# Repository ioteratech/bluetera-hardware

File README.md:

# Bluetera Hardware

This repository contains the KiCad project for the Bluetera II and it's breakout adapter.

Bluetera is an open source IoT platform for the development of smart and connected products. The platform includes:
* Bluetera Hardware module (this repository)
* Bluetera Firmware - repository [here](https://github.com/ioteratech/bluetera-firmware)
* Blutera SDK(s) - repositories [here](https://github.com/ioteratech/)

More info available at our website: https://ioteratech.com

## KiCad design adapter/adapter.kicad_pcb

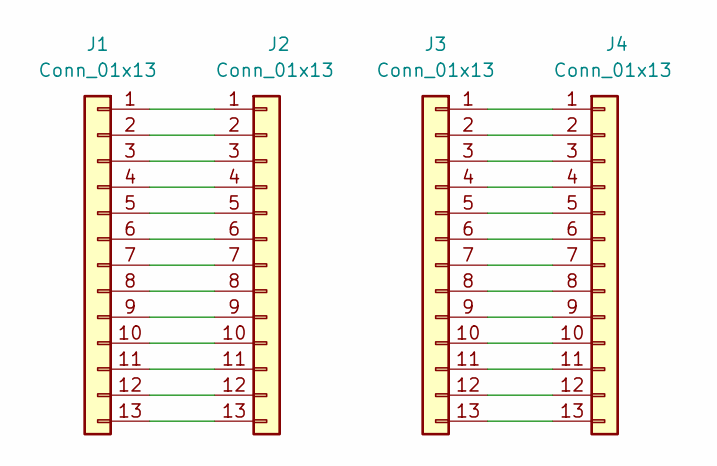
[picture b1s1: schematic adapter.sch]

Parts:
J1, J4: Conn_01x13; PinHeader_1x13_P2.54mm_Vertical
J2, J3: Conn_01x13; PinHeader_1x13_P1.27mm_Vertical

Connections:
unnamed: J1.1, J2.1
unnamed: J1.2, J2.2
unnamed: J1.3, J2.3
unnamed: J1.4, J2.4
unnamed: J1.5, J2.5
unnamed: J1.6, J2.6
unnamed: J1.7, J2.7
unnamed: J1.8, J2.8
unnamed: J1.9, J2.9
unnamed: J1.10, J2.10
unnamed: J1.11, J2.11
unnamed: J1.12, J2.12
unnamed: J1.13, J2.13
unnamed: J3.1, J4.1
unnamed: J3.2, J4.2
unnamed: J3.3, J4.3
unnamed: J3.4, J4.4
unnamed: J3.5, J4.5
unnamed: J3.6, J4.6
unnamed: J3.7, J4.7
unnamed: J3.8, J4.8
unnamed: J3.9, J4.9
unnamed: J3.10, J4.10
unnamed: J3.11, J4.11
unnamed: J3.12, J4.12
unnamed: J3.13, J4.13

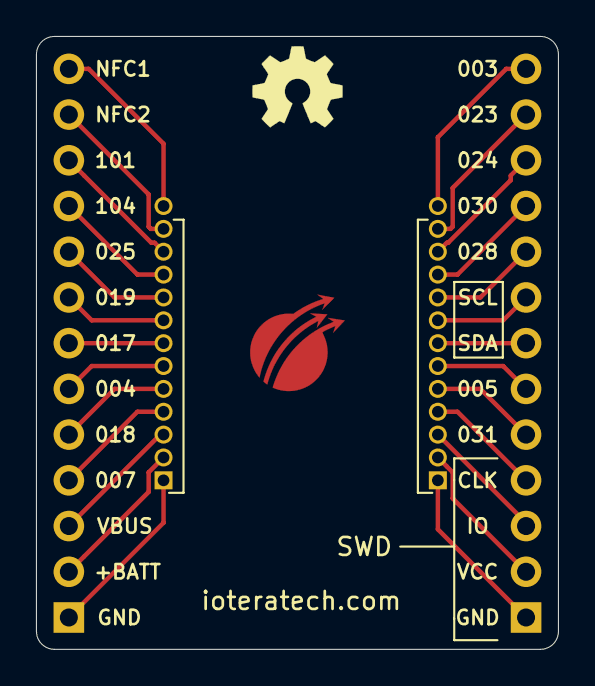
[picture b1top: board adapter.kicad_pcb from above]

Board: 2 copper layers, 29.0 x 34.0 mm, 4 parts (0 on the bottom side), 26 nets.

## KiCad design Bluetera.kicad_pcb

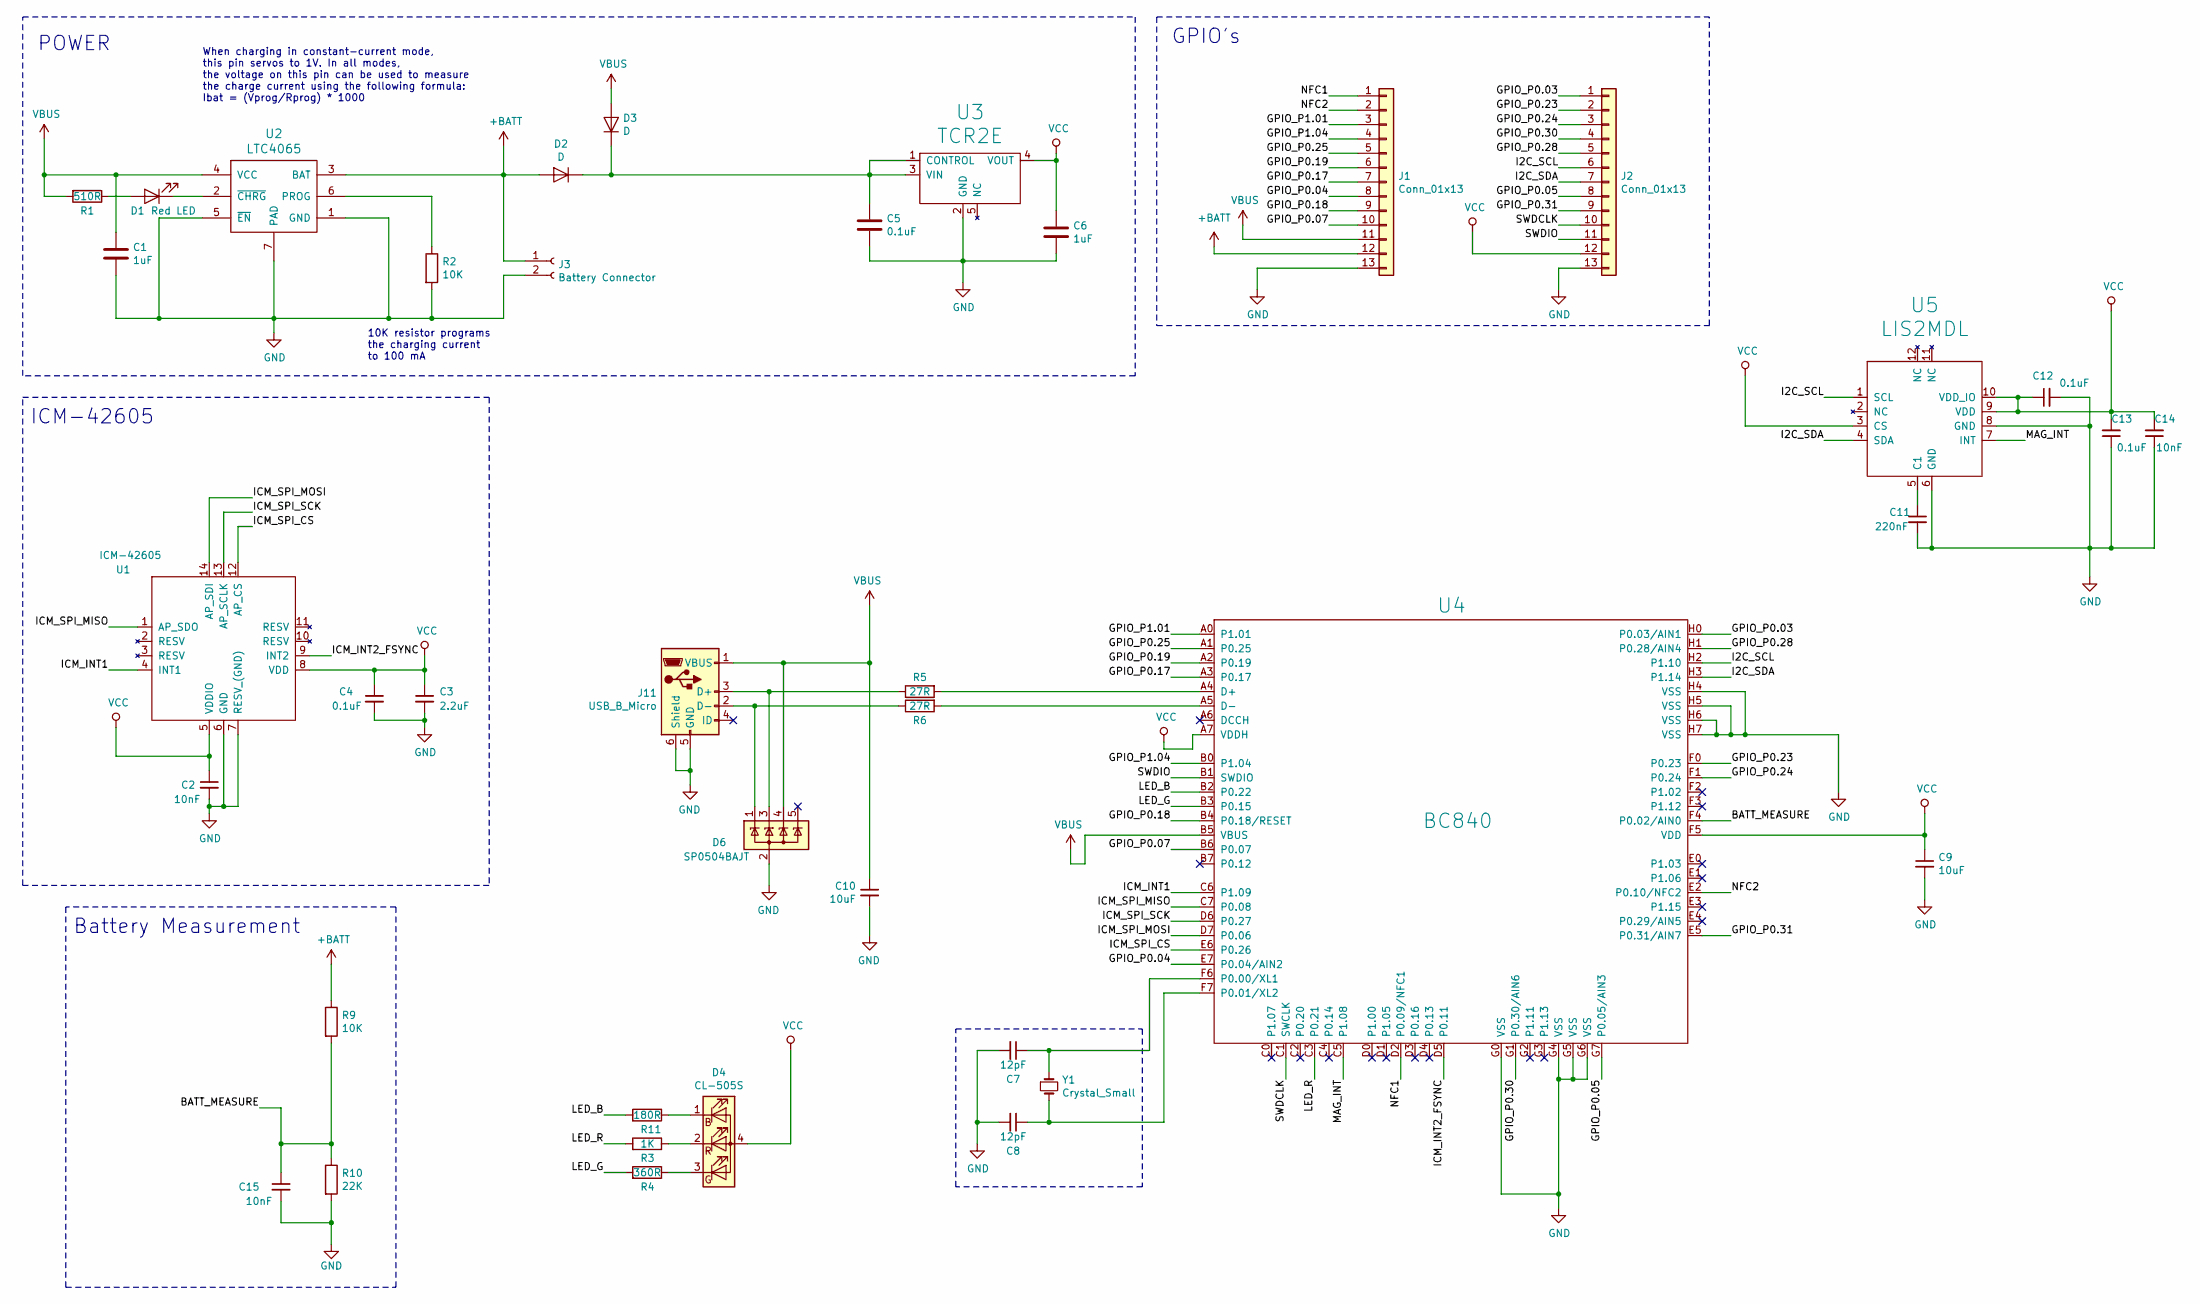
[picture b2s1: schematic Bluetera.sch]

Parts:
C1, C6: 1uF; C_0402_1005Metric; PartNumber C0402C105K9PACTU; DigikeyPartNumber 399-4873-1-ND
C2, C14: 10nF; C_0201_0603Metric; PartNumber CC0201KRX5R7BB103; DigikeyPartNumber 311-1596-1-ND
C3: 2.2uF; C_0201_0603Metric; PartNumber GRM033D80E225ME47D; DigikeyPartNumber 490-18653-1-ND
C4, C12, C13: 0.1uF; C_0201_0603Metric; PartNumber GRM033R61A104ME15D; DigikeyPartNumber 490-5405-1-ND
C5: 0.1uF; C_0402_1005Metric; PartNumber CL05F104ZO5NNNC; DigikeyPartNumber 1276-1004-1-ND
C7, C8: 12pF; C_0402_1005Metric; PartNumber CC0402JRNPO9BN120; DigikeyPartNumber 311-1016-1-ND
C9, C10: 10uF; C_0402_1005Metric; PartNumber GRM155C80J106ME11J; DigikeyPartNumber 490-18210-1-ND
C11: 220nF; C_0201_0603Metric; PartNumber CC0201MRX5R5BB224; DigikeyPartNumber 311-1412-1-ND
C15: 10nF; C_0402_1005Metric; PartNumber CC0201KRX5R7BB103; DigikeyPartNumber 311-1596-1-ND
D1: Red LED; LED_0603_1608Metric; PartNumber 150060RS75000; DigikeyPartNumber 732-4978-1-ND
D2, D3: D; D_SOD-523; PartNumber RB521S30T1G; DigikeyPartNumber RB521S30T1GOSCT-ND
D4: CL-505S; HSMF-C116; PartNumber CL-505S-X-SD-T; DigikeyPartNumber 1642-1510-1-ND
D6: SP0504BAJT; SOT-353_SC-70-5; PartNumber SP0504BAJTG; DigikeyPartNumber F3159CT-ND
J1, J2: Conn_01x13; PinHeader_1x13_P1.27mm_Vertical
J3: Battery Connector; JST_SH_SM02B-SRSS-TB_1x02-1MP_P1.00mm_Horizontal; PartNumber SM02B-SRSS-TB(LF)(SN); DigikeyPartNumber 455-1802-1-ND
J11: USB_B_Micro; USB_Micro-B; PartNumber 10118194-0001LF; DigikeyPartNumber 609-4618-1-ND
R1: 510R; R_0402_1005Metric; PartNumber ERJ-2BQJR51X; DigikeyPartNumber P17352CT-ND
R2, R9: 10K; R_0402_1005Metric; PartNumber RC0402FR-0710KL; DigikeyPartNumber 311-10.0KLRCT-ND
R3: 1K; R_0201_0603Metric; PartNumber RC0201FR-071KL; DigikeyPartNumber 311-1KMCT-ND
R4: 360R; R_0201_0603Metric; PartNumber RC0201FR-07360RL; DigikeyPartNumber YAG2622CT-ND
R5, R6: 27R; R_0402_1005Metric; PartNumber ERJ-2RKF27R0X; DigikeyPartNumber P27.0LCT-ND
R10: 22K; R_0402_1005Metric; PartNumber CRGCQ0402F22K; DigikeyPartNumber A129643CT-ND
R11: 180R; R_0201_0603Metric; PartNumber RC0201FR-07180RL; DigikeyPartNumber YAG2450CT-ND
U1: ICM-42605; PartNumber ICM-42605; DigikeyPartNumber 1428-1152-1-ND
U2: LTC4065; DFN-6-1EP_2x2mm_P0.5mm_EP0.61x1.42mm; PartNumber LTC4065AEDC#TRMPBF; DigikeyPartNumber LTC4065AEDC#TRMPBFCT-ND
U3: TCR2E; SOT-553; PartNumber TCR2EE30,LM(CT; DigikeyPartNumber TCR2EE30LM(CTCT-ND
U4: BC840
U5: LIS2MDL; PQFN50P200X200X70-12N; PartNumber LIS2MDLTR; DigikeyPartNumber 497-17588-1-ND
Y1: Crystal_Small; Crystal_SMD_2012-2Pin_2.0x1.2mm; PartNumber ECS-.327-9-12R-TR; DigikeyPartNumber XC2745CT-ND

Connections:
+BATT: D2.2 (A), J1.12, J3.1, R9.1, U2.3 (BAT)
/BATT_MEASURE: C15.1, R9.2, R10.1, U4.F4 (P0.02/AIN0)
/GPIO_P0.03: J2.1, U4.H0 (P0.03/AIN1)
/GPIO_P0.04: J1.8, U4.E7 (P0.04/AIN2)
/GPIO_P0.05: J2.8, U4.G7 (P0.05/AIN3)
/GPIO_P0.07: J1.10, U4.B6 (P0.07)
/GPIO_P0.17: J1.7, U4.A3 (P0.17)
/GPIO_P0.18: J1.9, U4.B4 (P0.18/RESET)
/GPIO_P0.19: J1.6, U4.A2 (P0.19)
/GPIO_P0.23: J2.2, U4.F0 (P0.23)
/GPIO_P0.24: J2.3, U4.F1 (P0.24)
/GPIO_P0.25: J1.5, U4.A1 (P0.25)
/GPIO_P0.28: J2.5, U4.H1 (P0.28/AIN4)
/GPIO_P0.30: J2.4, U4.G1 (P0.30/AIN6)
/GPIO_P0.31: J2.9, U4.E5 (P0.31/AIN7)
/GPIO_P1.01: J1.3, U4.A0 (P1.01)
/GPIO_P1.04: J1.4, U4.B0 (P1.04)
/I2C_SCL: J2.6, U4.H2 (P1.10), U5.1 (SCL)
/I2C_SDA: J2.7, U4.H3 (P1.14), U5.4 (SDA)
/ICM_INT1: U1.4 (INT1), U4.C6 (P1.09)
/ICM_INT2_FSYNC: U1.9 (INT2), U4.D5 (P0.11)
/ICM_SPI_CS: U1.12 (AP_CS), U4.E6 (P0.26)
/ICM_SPI_MISO: U1.1 (AP_SDO), U4.C7 (P0.08)
/ICM_SPI_MOSI: U1.14 (AP_SDI), U4.D7 (P0.06)
/ICM_SPI_SCK: U1.13 (AP_SCLK), U4.D6 (P0.27)
/LED_B: R11.2, U4.B2 (P0.22)
/LED_G: R4.2, U4.B3 (P0.15)
/LED_R: R3.2, U4.C3 (P0.21)
/MAG_INT: U4.C5 (P1.08), U5.7 (INT)
/NFC1: J1.1, U4.D2 (P0.09/NFC1)
/NFC2: J1.2, U4.E2 (P0.10/NFC2)
/SWDCLK: J2.10, U4.C1 (SWCLK)
/SWDIO: J2.11, U4.B1 (SWDIO)
GND: C1.2, C2.2, C3.2, C4.2, C5.2, C6.2, C7.2, C8.2, C9.2, C10.2, C11.2, C12.2, C13.1, C14.1, C15.2, D6.2 (A), J1.13, J2.13, J3.2, J11.5 (GND), J11.6 (Shield), R2.2, R10.2, U1.6 (GND), U1.7 (RESV_(GND)), U2.1 (GND), U2.5 (~EN), U2.7 (PAD), U3.2 (GND), U4.G0 (VSS), U4.G4 (VSS), U4.G5 (VSS), U4.G6 (VSS), U4.H4 (VSS), U4.H5 (VSS), U4.H6 (VSS), U4.H7 (VSS), U5.6 (GND), U5.8 (GND)
unnamed: C5.1, D2.1 (K), D3.1 (K), U3.1 (CONTROL), U3.3 (VIN)
unnamed: C7.1, U4.F6 (P0.00/XL1), Y1.1
unnamed: C8.1, U4.F7 (P0.01/XL2), Y1.2
unnamed: C11.1, U5.5 (C1)
unnamed: D1.1 (K), U2.2 (~CHRG)
unnamed: D1.2 (A), R1.1
unnamed: D4.1 (BK), R11.1
unnamed: D4.2 (RK), R3.1
unnamed: D4.3 (GK), R4.1
unnamed: D6.1 (K), J11.2 (D-), R6.1
unnamed: D6.3 (K), J11.3 (D+), R5.1
unnamed: R2.1, U2.6 (PROG)
unnamed: R5.2, U4.A4 (D+)
unnamed: R6.2, U4.A5 (D-)
VBUS: C1.1, C10.1, D3.2 (A), D6.4 (K), J1.11, J11.1 (VBUS), R1.2, U2.4 (VCC), U4.B5 (VBUS)
VCC: C2.1, C3.1, C4.1, C6.1, C9.1, C12.1, C13.2, C14.2, D4.4 (A), J2.12, U1.5 (VDDIO), U1.8 (VDD), U3.4 (VOUT), U4.A7 (VDDH), U4.F5 (VDD), U5.3 (CS), U5.9 (VDD), U5.10 (VDD_IO)

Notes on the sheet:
ICM-42605
10K resistor programs the charging current to 100 mA
When charging in constant-current mode, this pin servos to 1V. In all modes, the voltage on this pin can be used to measure the charge current using the following formula: Ibat = (Vprog/Rprog) * 1000
GPIO's
Battery Measurement
POWER

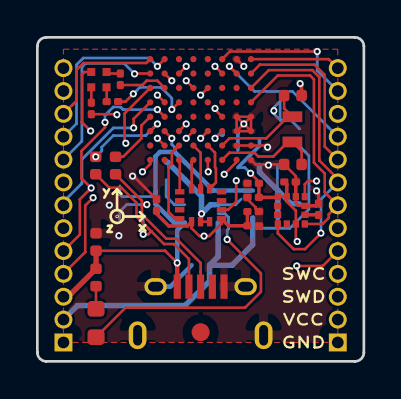
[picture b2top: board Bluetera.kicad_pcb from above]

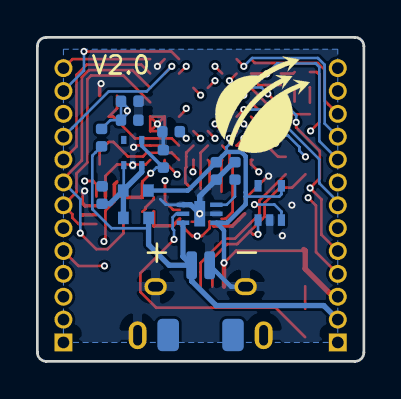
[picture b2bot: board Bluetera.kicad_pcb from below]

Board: 4 copper layers, 18.1 x 18.0 mm, 39 parts (16 on the bottom side), 50 nets.

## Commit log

2020-01-26 initial project commit
2020-01-26 decreased logo size in README
2020-01-26 space
